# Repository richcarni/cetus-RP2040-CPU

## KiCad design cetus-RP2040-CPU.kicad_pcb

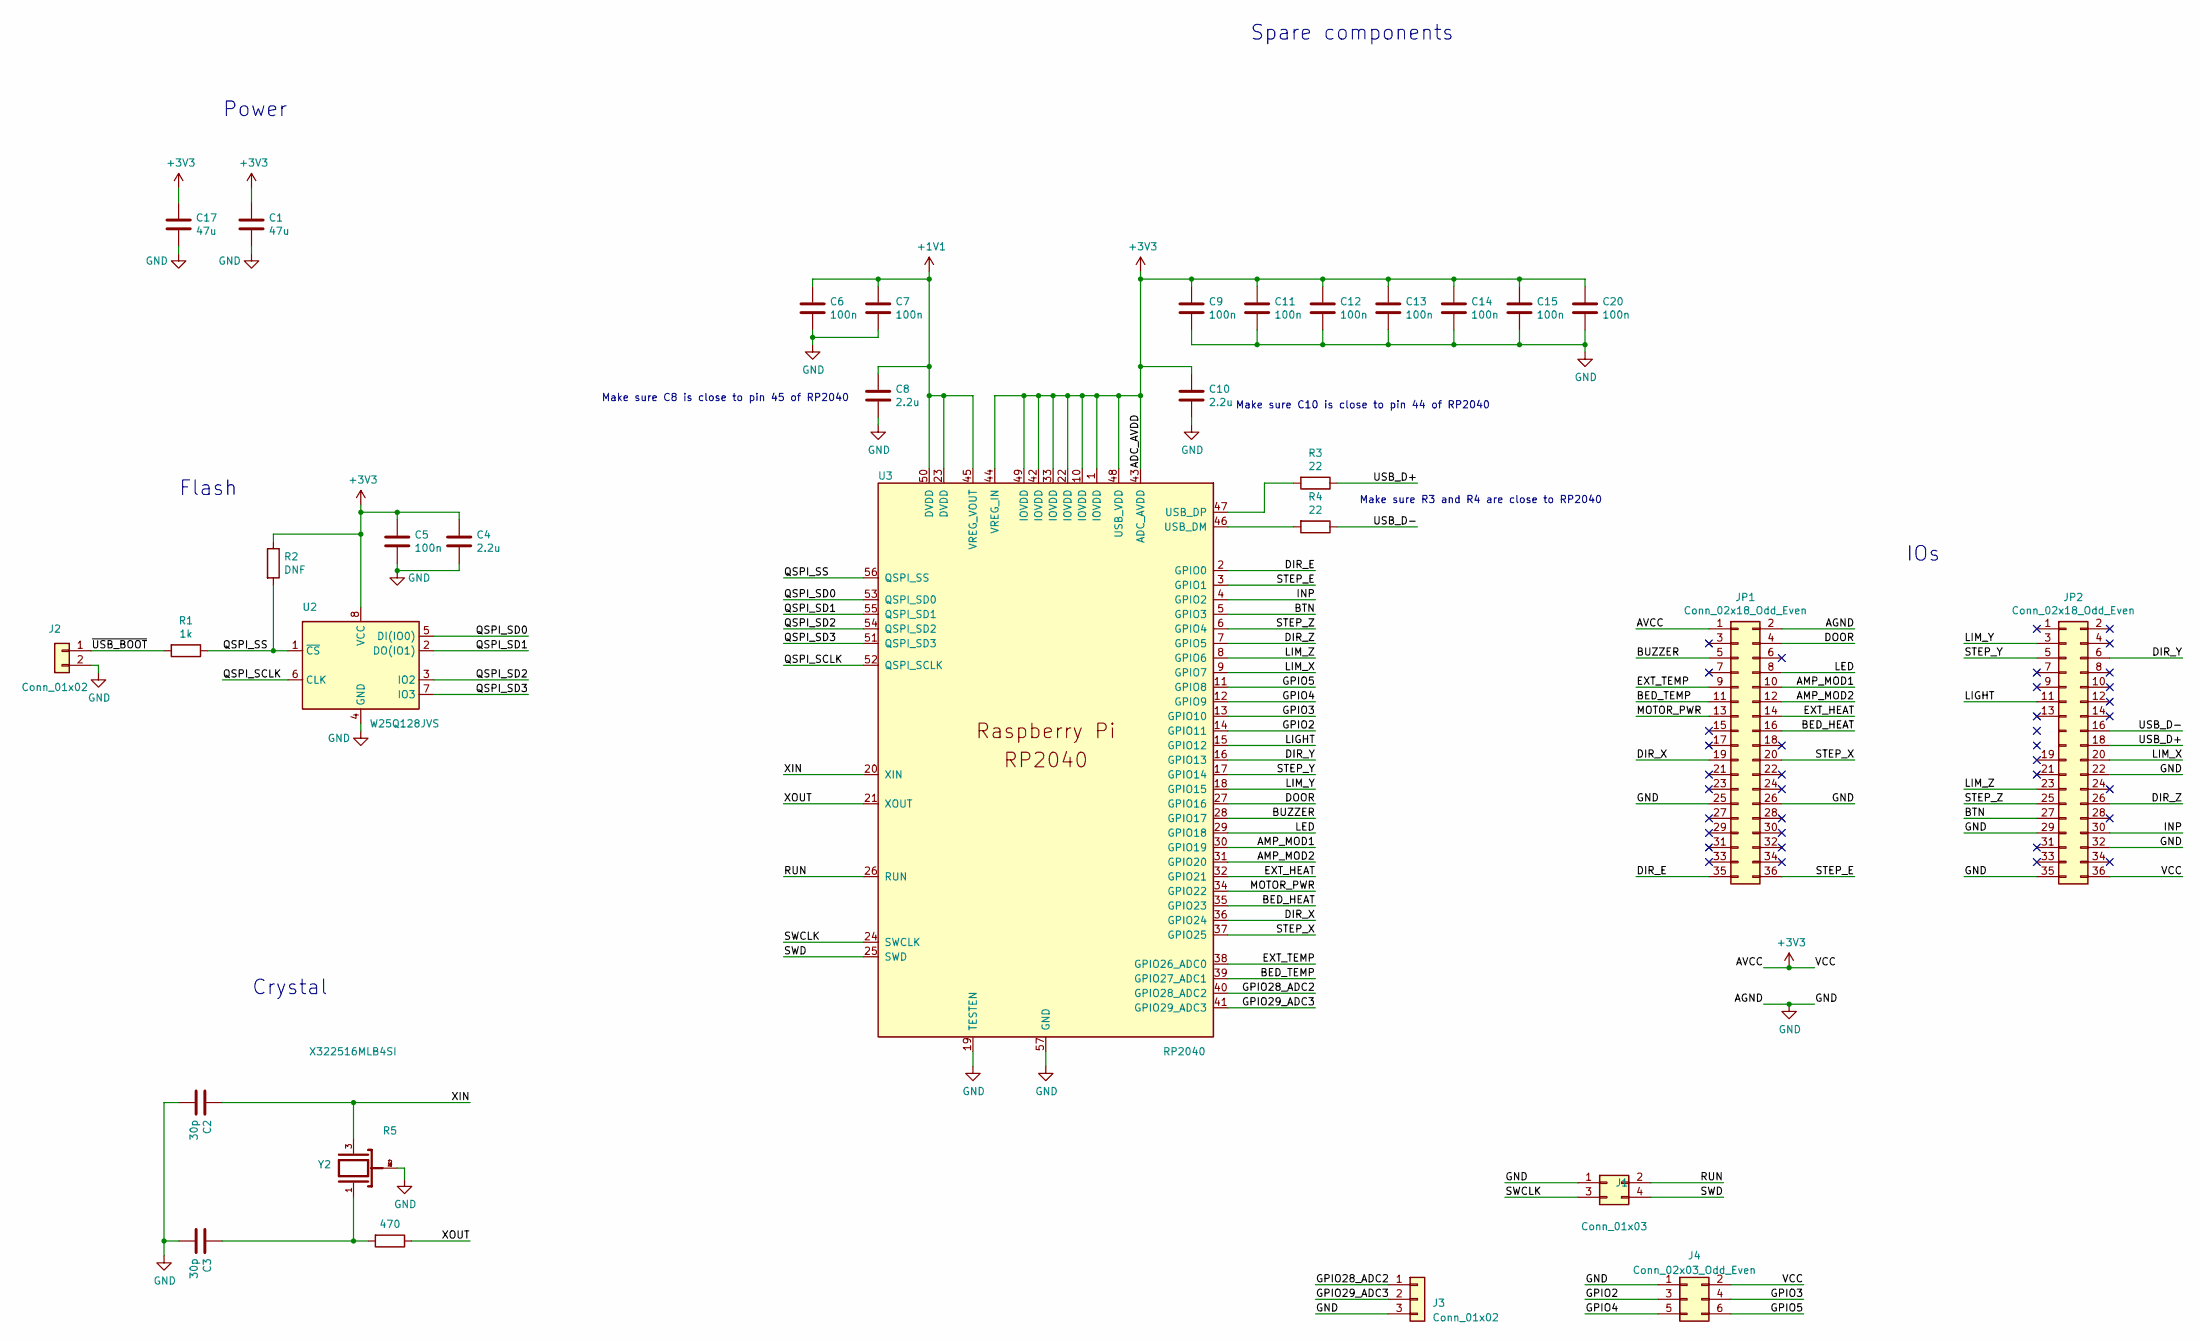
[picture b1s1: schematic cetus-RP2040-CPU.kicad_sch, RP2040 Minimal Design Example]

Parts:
C1, C17: 47u; C_0805_2012Metric
C2, C3: 30p; C_0402_1005Metric
C4, C8, C10: 2.2u; C_0402_1005Metric
C5, C6, C7, C9, C11, C12, C13, C14, C15, C20: 100n; C_0402_1005Metric
J1: Conn_01x03; PinHeader_2x02_P2.54mm_Vertical
J2: Conn_01x02; PinHeader_1x02_P2.54mm_Vertical
J3: Conn_01x02; PinHeader_1x03_P2.54mm_Vertical
J4: Conn_02x03_Odd_Even; PinHeader_2x03_P2.54mm_Vertical
JP1: Conn_02x18_Odd_Even; PinHeader_2x18_P2.54mm_Vertical_backside
JP2: Conn_02x18_Odd_Even; PinHeader_2x18_P2.54mm_Vertical_backside_pads15+17_removed
R1: 1k; R_0402_1005Metric
R2: DNF; R_0402_1005Metric
R3, R4: 22; R_0402_1005Metric
R5: 470; R_0402_1005Metric
U2: W25Q128JVS; SOIC-8_5.23x5.23mm_P1.27mm+model
U3: RP2040; RP2040-QFN-56
Y2: X322516MLB4SI; OSC_X322516MLB4SI; PARTREV N/A

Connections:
+1V1: C6.1, C7.1, C8.1, U3.23 (DVDD), U3.45 (VREG_VOUT), U3.50 (DVDD)
+3V3: C1.1, C4.1, C5.1, C9.1, C10.1, C11.1, C12.1, C13.1, C14.1, C15.1, C17.1, C20.1, J4.2, JP1.1, JP2.36, R2.1, U2.8 (VCC), U3.1 (IOVDD), U3.10 (IOVDD), U3.22 (IOVDD), U3.33 (IOVDD), U3.42 (IOVDD), U3.43 (ADC_AVDD), U3.44 (VREG_IN), U3.48 (USB_VDD), U3.49 (IOVDD)
/AMP_MOD1: JP1.10, U3.30 (GPIO19)
/AMP_MOD2: JP1.12, U3.31 (GPIO20)
/BED_HEAT: JP1.16, U3.35 (GPIO23)
/BED_TEMP: JP1.11, U3.39 (GPIO27_ADC1)
/BTN: JP2.27, U3.5 (GPIO3)
/BUZZER: JP1.5, U3.28 (GPIO17)
/DIR_E: JP1.35, U3.2 (GPIO0)
/DIR_X: JP1.19, U3.36 (GPIO24)
/DIR_Y: JP2.6, U3.16 (GPIO13)
/DIR_Z: JP2.26, U3.7 (GPIO5)
/DOOR: JP1.4, U3.27 (GPIO16)
/EXT_HEAT: JP1.14, U3.32 (GPIO21)
/EXT_TEMP: JP1.9, U3.38 (GPIO26_ADC0)
/GPIO2: J4.3, U3.14 (GPIO11)
/GPIO3: J4.4, U3.13 (GPIO10)
/GPIO4: J4.5, U3.12 (GPIO9)
/GPIO5: J4.6, U3.11 (GPIO8)
/GPIO28_ADC2: J3.1, U3.40 (GPIO28_ADC2)
/GPIO29_ADC3: J3.2, U3.41 (GPIO29_ADC3)
/INP: JP2.30, U3.4 (GPIO2)
/LED: JP1.8, U3.29 (GPIO18)
/LIGHT: JP2.11, U3.15 (GPIO12)
/LIM_X: JP2.20, U3.9 (GPIO7)
/LIM_Y: JP2.3, U3.18 (GPIO15)
/LIM_Z: JP2.23, U3.8 (GPIO6)
/MOTOR_PWR: JP1.13, U3.34 (GPIO22)
/QSPI_SCLK: U2.6 (CLK), U3.52 (QSPI_SCLK)
/QSPI_SD0: U2.5 (DI(IO0)), U3.53 (QSPI_SD0)
/QSPI_SD1: U2.2 (DO(IO1)), U3.55 (QSPI_SD1)
/QSPI_SD2: U2.3 (IO2), U3.54 (QSPI_SD2)
/QSPI_SD3: U2.7 (IO3), U3.51 (QSPI_SD3)
/QSPI_SS: R1.1, R2.2, U2.1 (~CS), U3.56 (QSPI_SS)
/RUN: J1.2, U3.26 (RUN)
/STEP_E: JP1.36, U3.3 (GPIO1)
/STEP_X: JP1.20, U3.37 (GPIO25)
/STEP_Y: JP2.5, U3.17 (GPIO14)
/STEP_Z: JP2.25, U3.6 (GPIO4)
/SWCLK: J1.3, U3.24 (SWCLK)
/SWD: J1.4, U3.25 (SWD)
/USB_D+: JP2.18, R3.1
/USB_D-: JP2.16, R4.1
/XIN: C2.1, U3.20 (XIN), Y2.3
/XOUT: R5.1, U3.21 (XOUT)
/~USB_BOOT: J2.1, R1.2
GND: C1.2, C2.2, C3.2, C4.2, C5.2, C6.2, C7.2, C8.2, C9.2, C10.2, C11.2, C12.2, C13.2, C14.2, C15.2, C17.2, C20.2, J1.1, J2.2, J3.3, J4.1, JP1.2, JP1.25, JP1.26, JP2.22, JP2.29, JP2.32, JP2.35, U2.4 (GND), U3.19 (TESTEN), U3.57 (GND), Y2.2, Y2.4
unnamed: C3.1, R5.2, Y2.1
unnamed: R4.2, U3.46 (USB_DM)
unnamed: R3.2, U3.47 (USB_DP)

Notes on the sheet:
Make sure C8 is close to pin 45 of RP2040
Make sure C10 is close to pin 44 of RP2040
Flash
IOs
Spare components
Crystal
Power
Make sure R3 and R4 are close to RP2040

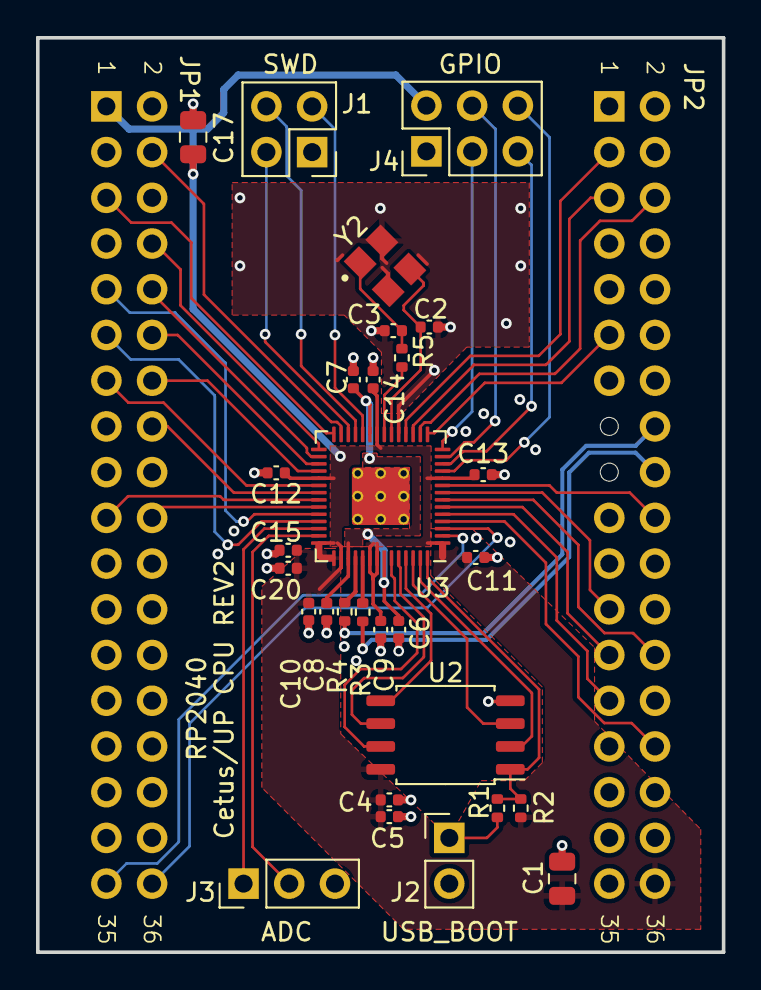
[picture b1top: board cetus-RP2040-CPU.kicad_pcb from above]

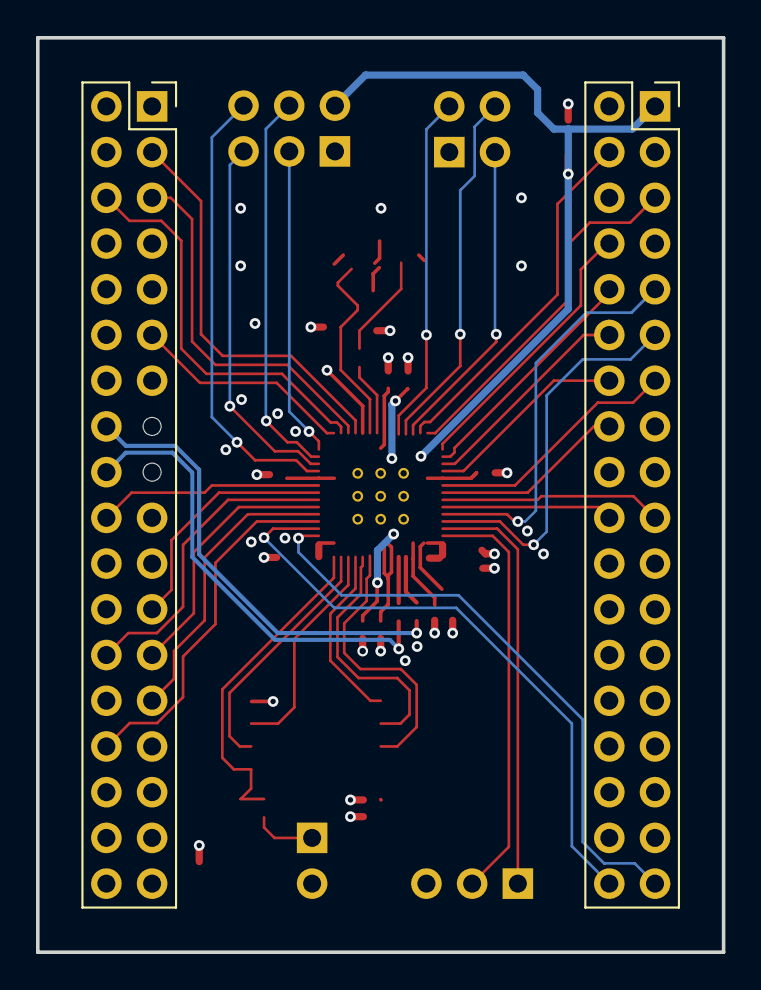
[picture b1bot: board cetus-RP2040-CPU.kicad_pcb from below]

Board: 4 copper layers, 38.1 x 50.8 mm, 31 parts (2 on the bottom side), 50 nets.

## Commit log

2023-06-29 Board ready for production, tab on bottom
2023-06-30 First production batch sent to JLCPCB
2023-06-30 README.md created online with Bitbucket
2023-06-30 Add board image for README
2023-06-30 README.md edited online with Bitbucket
2023-06-30 Crop 3D board image (README.md)
2023-07-01 Add JLCPCB bom
    This should be used to specify components in schematic (and therefore add part numbers to kicad generated bom)
2023-07-29 Remove/exclude RP2040_minimal.kicad_prl from repo
2023-07-29 Update README.md for github
2023-07-31 Rename KiCad project
    Project name is now cetus-RP2040-CPU
    Also deleted bom and part position files in preparation to minor board modfications
2023-07-31 Remove spare components and break-off tab
    Also, fix PCB DRC errors/warnings:
    - Create a custom symbol for header to match footprint with missing pads
    - Create footprints for flash and crystal which have 3D models
2023-07-31 Fix silkscreen crystal designation text size
2023-08-01 Update README to rev2
    - Fix crystal footprint: add 3D model
    - Generate new 3D view
2023-08-01 Remove black border from 3D view
